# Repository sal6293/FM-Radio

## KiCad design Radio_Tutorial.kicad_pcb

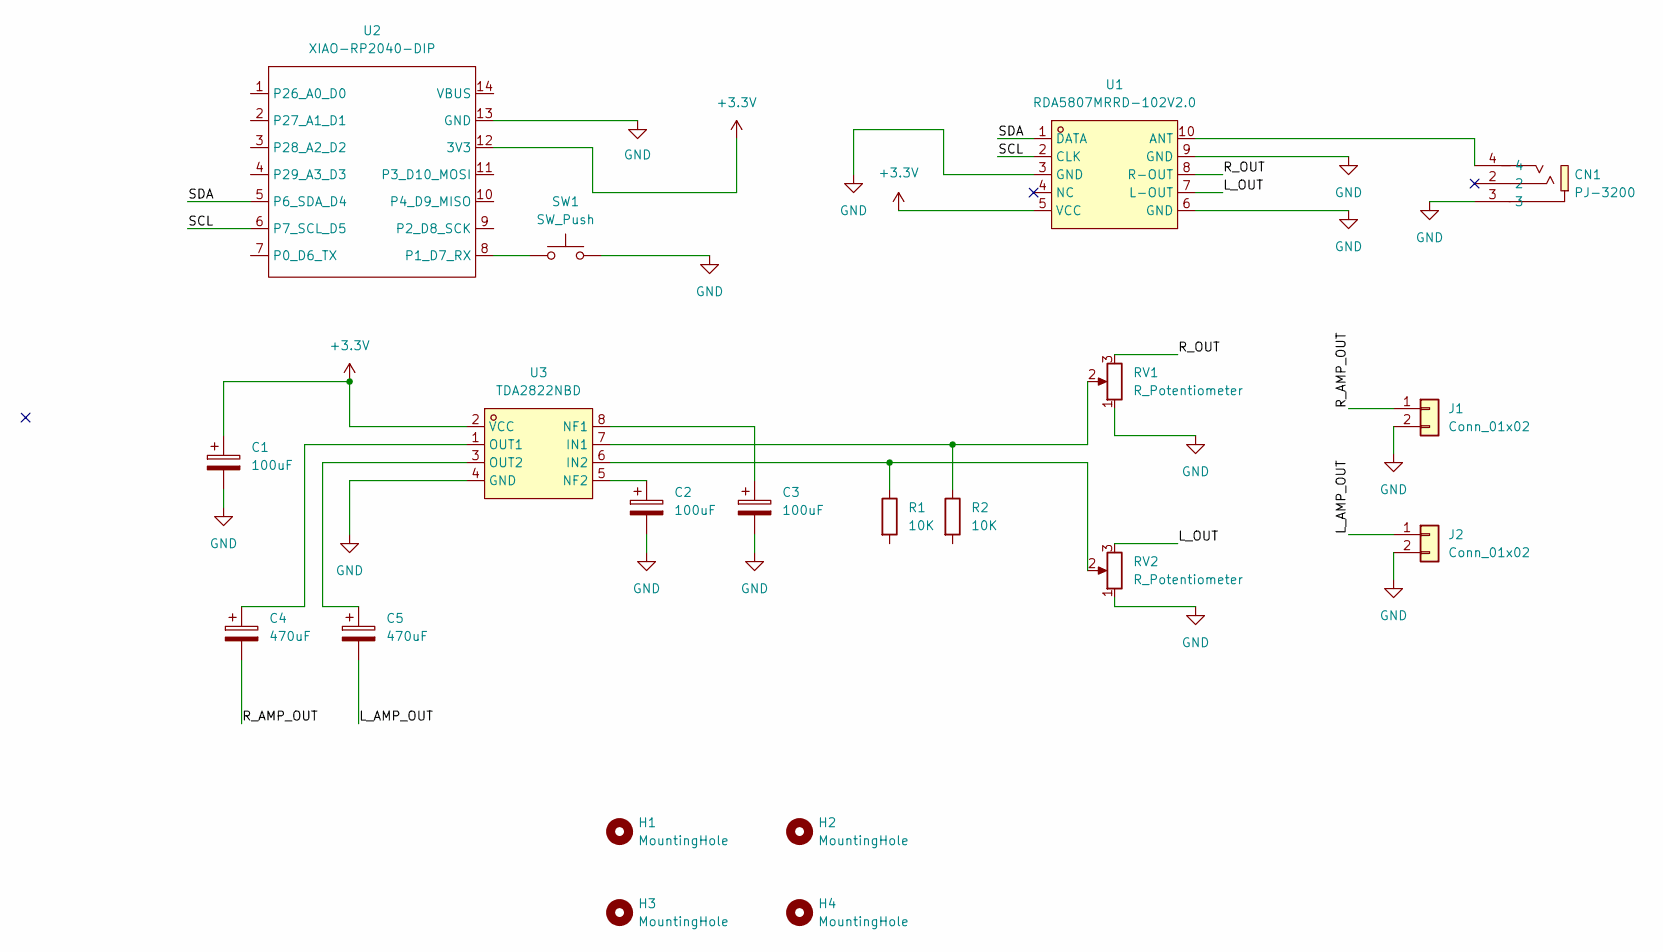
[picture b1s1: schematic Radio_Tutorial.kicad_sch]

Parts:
C1, C2, C3: 100uF; CP_Radial_D6.3mm_P2.50mm
C4, C5: 470uF; CP_Radial_D6.3mm_P2.50mm
CN1: PJ-3200; AUDIO-TH_PJ-3200; MPN PJ-3200; LCSC Part C2689690
H1, H2, H3, H4: MountingHole; MountingHole_2.7mm_M2.5
J1, J2: Conn_01x02; PinHeader_1x02_P2.54mm_Vertical
R1, R2: 10K; R_Axial_DIN0207_L6.3mm_D2.5mm_P7.62mm_Horizontal
RV1, RV2: R_Potentiometer; PinHeader_1x03_P2.54mm_Vertical
SW1: SW_Push; PinHeader_1x02_P2.54mm_Vertical
U1: RDA5807MRRD-102V2.0; RDA5807; MPN RDA5807MRRD-102V2.0; LCSC Part C9900205627
U2: XIAO-RP2040-DIP
U3: TDA2822NBD; DIP-8_W7.62mm; MPN TDA2822NBD; LCSC Part C51927337

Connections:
+3.3V: C1.1, U1.5 (VCC), U2.12 (3V3), U3.2 (VCC)
/L_AMP_OUT: C5.2, J2.1
/L_OUT: RV2.3, U1.7 (L-OUT)
/R_AMP_OUT: C4.2, J1.1
/R_OUT: RV1.3, U1.8 (R-OUT)
/SCL: U1.2 (CLK), U2.6 (P7_SCL_D5)
/SDA: U1.1 (DATA), U2.5 (P6_SDA_D4)
GND: C1.2, C2.2, C3.2, CN1.3, J1.2, J2.2, RV1.1, RV2.1, SW1.2, U1.3 (GND), U1.6 (GND), U1.9 (GND), U2.13 (GND), U3.4 (GND)
unnamed: CN1.4, U1.10 (ANT)
unnamed: SW1.1, U2.8 (P1_D7_RX)
unnamed: R2.1, RV1.2, U3.7 (IN1)
unnamed: R1.1, RV2.2, U3.6 (IN2)
unnamed: C3.1, U3.8 (NF1)
unnamed: C2.1, U3.5 (NF2)
unnamed: C4.1, U3.1 (OUT1)
unnamed: C5.1, U3.3 (OUT2)

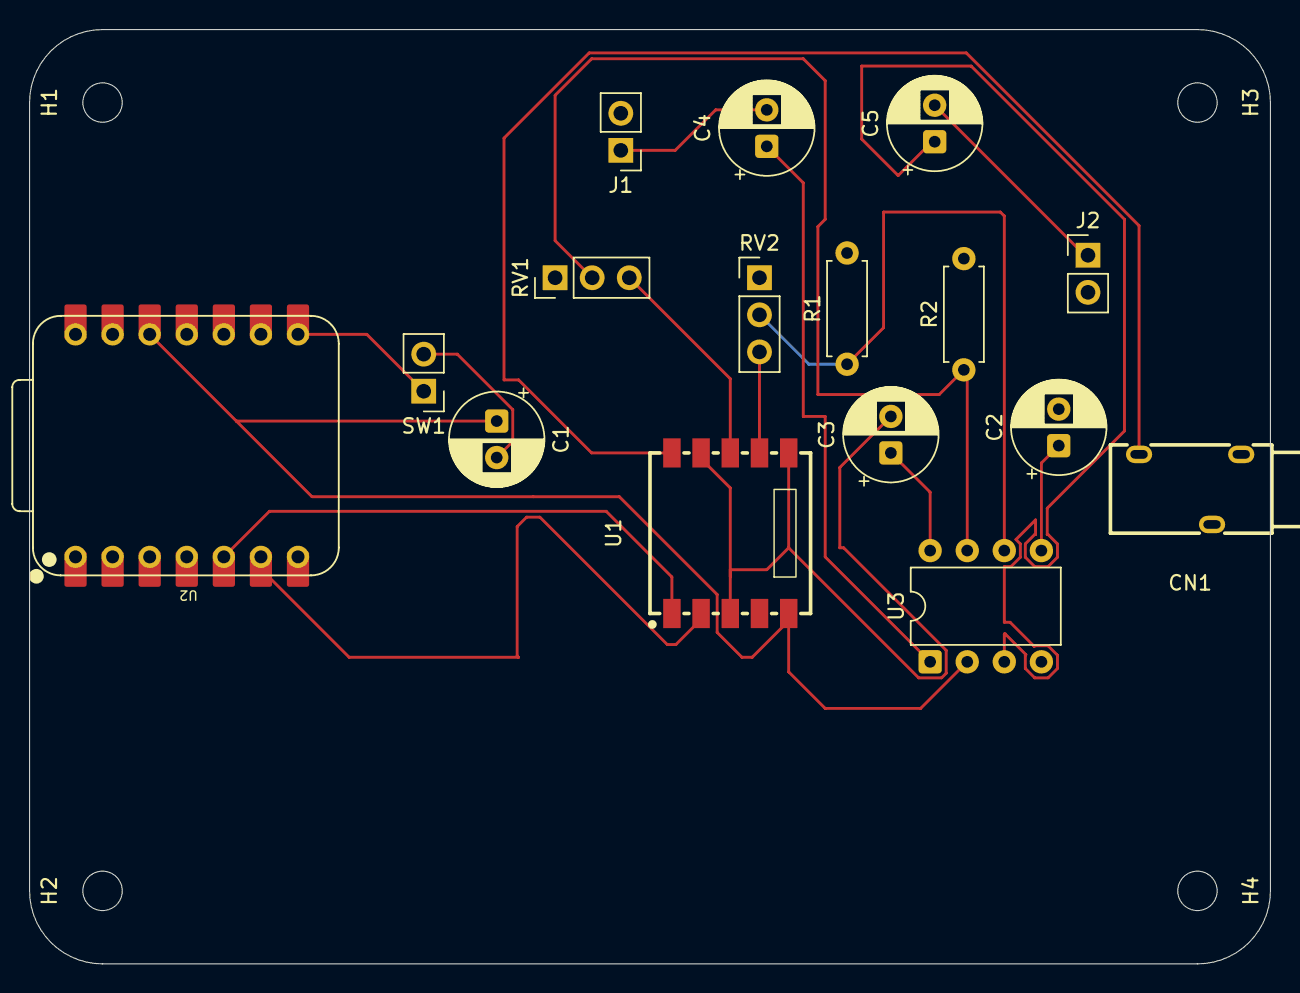
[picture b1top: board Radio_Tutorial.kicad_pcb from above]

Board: 2 copper layers, 85.0 x 64.0 mm, 20 parts (0 on the bottom side), 16 nets.
